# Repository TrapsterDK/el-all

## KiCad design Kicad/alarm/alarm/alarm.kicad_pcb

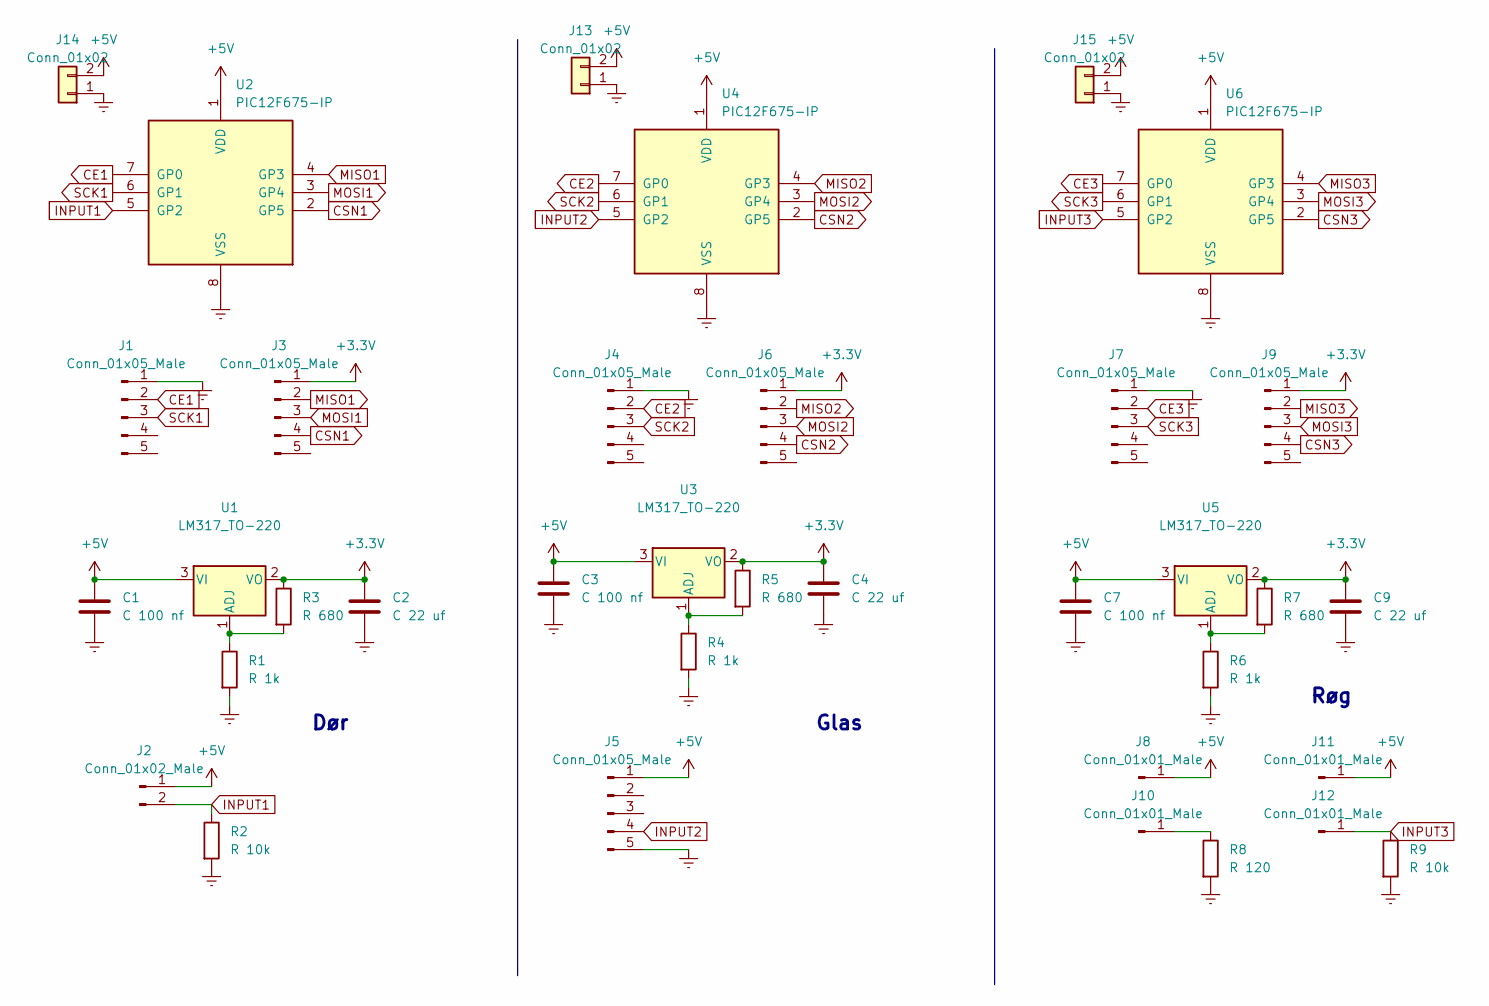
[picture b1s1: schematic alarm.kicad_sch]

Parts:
C1, C3, C7: C 100 nf; C_7.50mm
C2, C4, C9: C 22 uf; C_7.50mm
J1, J3, J4, J5, J6, J7, J9: Conn_01x05_Male; 1x05
J2: Conn_01x02_Male; 1x02
J8, J10, J11, J12: Conn_01x01_Male; PinHeader_1x01_P2.54mm_Vertical
J13, J14, J15: Conn_01x02; 1x02
R1, R4, R6: R 1k; R_lodret
R2, R9: R 10k; R_lodret
R3, R5, R7: R 680; R_lodret
R8: R 120; R_lodret
U1, U3, U5: LM317_TO-220; TO-220-lodret
U2, U4, U6: PIC12F675-IP; DIP-8

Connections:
+3.3V: C2.1, C4.1, C9.1, J3.1, J6.1, J9.1, R3.1, R5.1, R7.1, U1.2 (VO), U3.2 (VO), U5.2 (VO)
+5V: C1.1, C3.1, C7.1, J2.1, J5.1, J8.1, J11.1, J13.2, J14.2, J15.2, U1.3 (VI), U2.1 (VDD), U3.3 (VI), U4.1 (VDD), U5.3 (VI), U6.1 (VDD)
CE1: J1.2, U2.7 (GP0)
CE2: J4.2, U4.7 (GP0)
CE3: J7.2, U6.7 (GP0)
CSN1: J3.4, U2.2 (GP5)
CSN2: J6.4, U4.2 (GP5)
CSN3: J9.4, U6.2 (GP5)
Earth: C1.2, C2.2, C3.2, C4.2, C7.2, C9.2, J1.1, J4.1, J5.5, J7.1, J13.1, J14.1, J15.1, R1.2, R2.2, R4.2, R6.2, R8.2, R9.2, U2.8 (VSS), U4.8 (VSS), U6.8 (VSS)
INPUT1: J2.2, R2.1, U2.5 (GP2)
INPUT2: J5.4, U4.5 (GP2)
INPUT3: J12.1, R9.1, U6.5 (GP2)
MISO1: J3.2, U2.4 (GP3)
MISO2: J6.2, U4.4 (GP3)
MISO3: J9.2, U6.4 (GP3)
MOSI1: J3.3, U2.3 (GP4)
MOSI2: J6.3, U4.3 (GP4)
MOSI3: J9.3, U6.3 (GP4)
unnamed: J10.1, R8.1
unnamed: R1.1, R3.2, U1.1 (ADJ)
unnamed: R4.1, R5.2, U3.1 (ADJ)
unnamed: R6.1, R7.2, U5.1 (ADJ)
SCK1: J1.3, U2.6 (GP1)
SCK2: J4.3, U4.6 (GP1)
SCK3: J7.3, U6.6 (GP1)

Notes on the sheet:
Dør
Glas
Røg

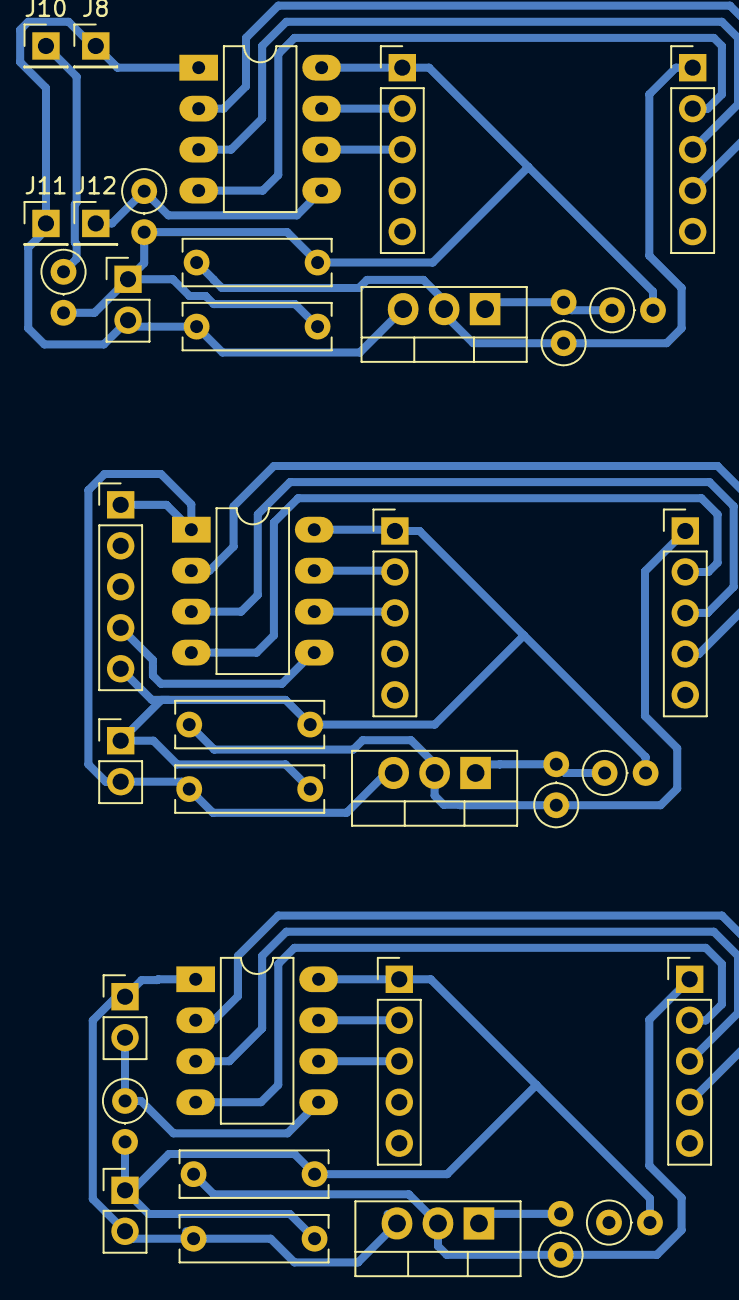
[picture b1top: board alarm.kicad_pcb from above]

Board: 2 copper layers, 36 parts (0 on the bottom side), 25 nets.

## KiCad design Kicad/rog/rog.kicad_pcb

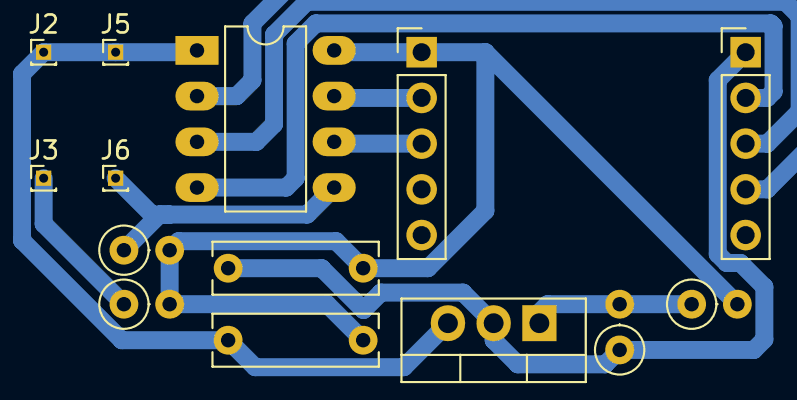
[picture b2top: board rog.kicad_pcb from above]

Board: 2 copper layers, 14 parts (0 on the bottom side), 11 nets.

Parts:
C1: C 100 nf; C_7.50mm
C2: C 22 uf; C_7.50mm
J1, J4: Conn_01x05_Male; 1x05
J2, J3, J5, J6: Conn_01x01_Male; PinHeader_1x01_P1.00mm_Vertical
R1: R 1k; R_lodret
R2: R 120; R_lodret
R3: R 680; R_lodret
R4: R 10k; R_lodret
U1: PIC12F675-IP; DIP-8
U2: LM317_TO-220; TO-220-lodret

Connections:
+3.3V: C2.1, J4.1, R3.1, U2.2 (VO)
+5V: C1.1, J2.1, J5.1, U1.1 (VDD), U2.3 (VI)
CE: J1.2, U1.7 (GP0)
CSN: J4.4, U1.2 (GP5)
Earth: C1.2, C2.2, J1.1, R1.2, R2.2, R4.2, U1.8 (VSS)
INPUT: J6.1, R4.1, U1.5 (GP2)
MISO: J4.2, U1.4 (GP3)
MOSI: J4.3, U1.3 (GP4)
unnamed: J3.1, R2.1
unnamed: R1.1, R3.2, U2.1 (ADJ)
SCK: J1.3, U1.6 (GP1)

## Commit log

2022-08-23 nrf24 discribtion
2022-08-23 nrf24 data added
2022-08-24 SPI implementation, radio begun, documentation
2022-08-24 radio working in theory
2022-08-25 fixed wrong gate when read writing to radio
2022-08-25 make ss auto handled
2022-08-25 radio convertion to header file
2022-09-23 SUSY BACKA
2022-09-23 Bil done
2022-09-25 Code comments
2023-03-27 working
2023-03-27 software attempt
2023-03-27 asda
2023-04-19 some working
